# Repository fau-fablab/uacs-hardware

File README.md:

uacs
====

An universal access control system.

Usecase(s)
----------

* machine access control system:
  * monitor access to the machine
  * monitor the machine use time and whether the machine is in use or not
  * add the possibility to reserve machines
  * add a dead man's switch to the machine (force the user to interact with the uacs terminal every x minutes)

Features
--------

* [2.8" Touchscreen](../v2.0/pcb/datasheets/ILI9341.pdf)
* [ISO/IEC 14443A/MIFARE Reader/Writer (supports e.g. MIFARE Classic + DESFire)](../v2.0/pcb/datasheets/PN532-short.pdf)
* [ethernet-access](../v2.0/pcb/datasheets/W5100.pdf)
* powered via 2.1mm DC-Jack (Voltage: 7-50V) or passive POE (power over ethernet)
* micro-sd-card reader to store data (lcd-background images, caching of authorized rfid cards, ..)
* multiple IOs (I²C, UART, SPI, digital/analog pins e.g. to control relais or get sensor values)
* (piezo-)speaker for audio feedback
* real time clock

Remark
------

Development is still in progress, this is not a final version!<br />
If you want to contribute, take a look at the [wiki](https://github.com/fau-fablab/uacs/wiki/Contribution).

PCB
---

The terminal is built from two stacked pcbs in order to save space.<br />
Eagle Layout files and datasheets of used components can be found under [/pcb](../v2.0/pcb).

Firmware
--------

The firmware is written in arduino (c/c++) since the pcb is arduino mega compatible.<br />
The backend is (not yet ;)) written in Python.<br />
All code can be found under [/firmware](../v2.0/firmware).

License
-------

<br />This work is licensed under a <a rel="license" href="http://creativecommons.org/licenses/by-sa/4.0/">Creative Commons Attribution-ShareAlike 4.0 International License</a>.

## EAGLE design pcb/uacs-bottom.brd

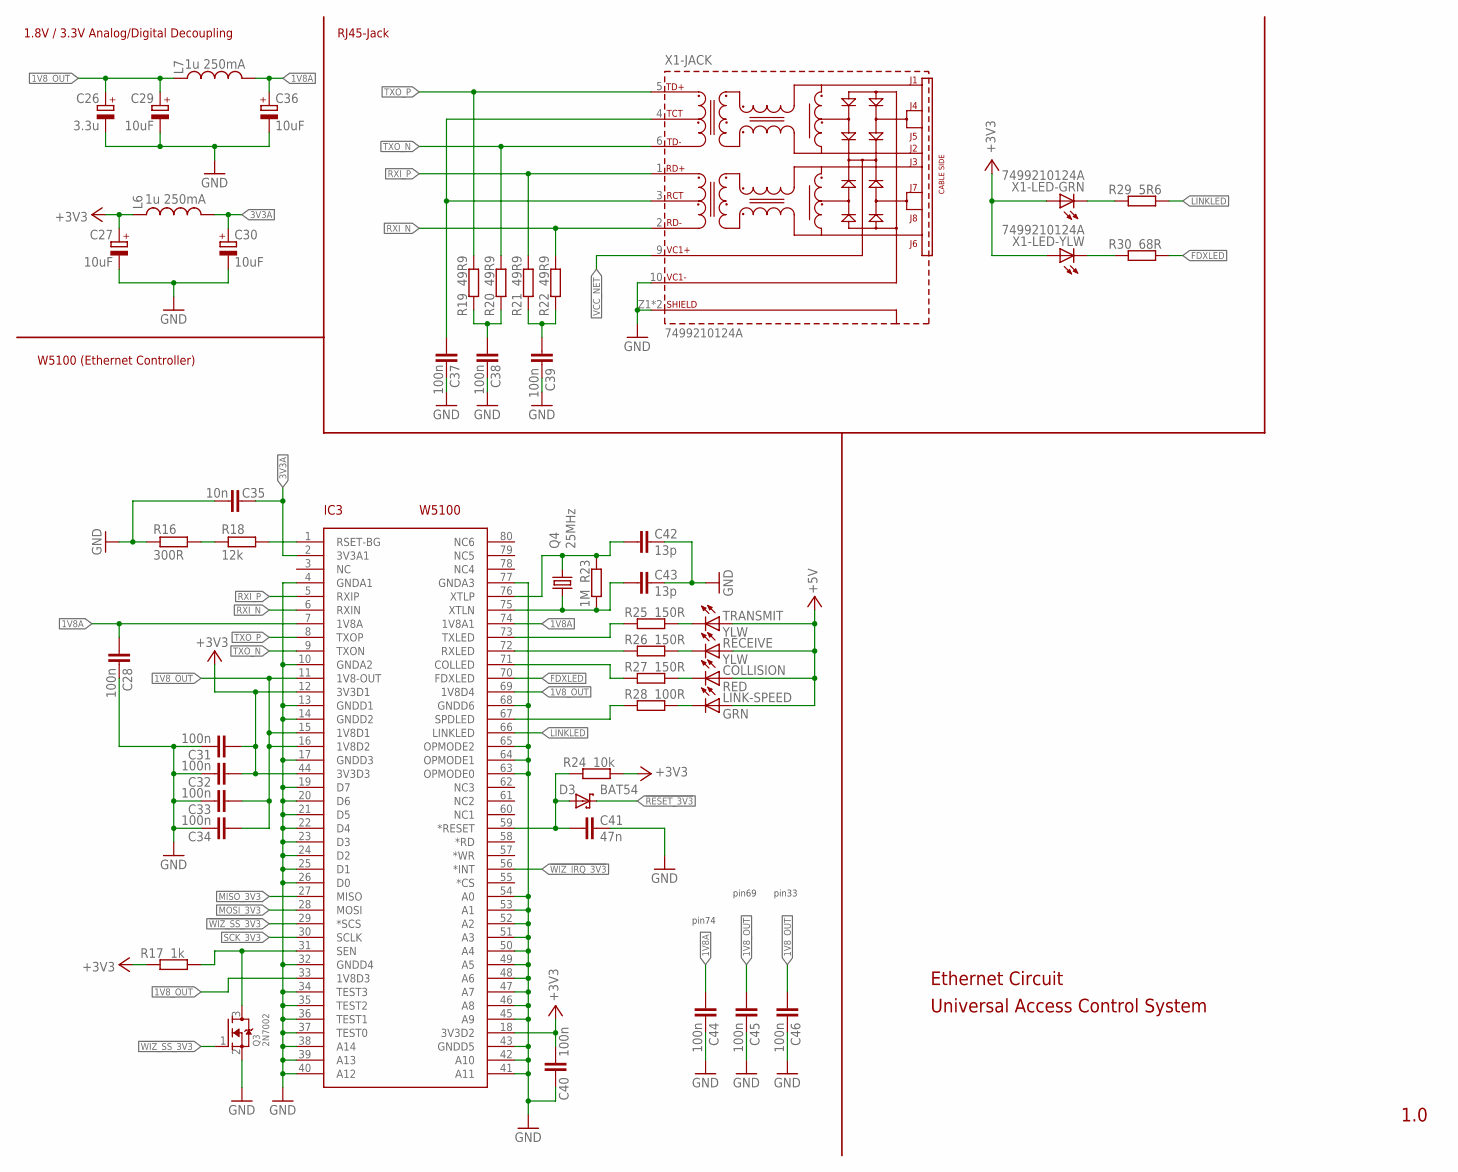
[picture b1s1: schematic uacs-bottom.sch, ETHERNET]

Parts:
C26: 3.3u; B/3528-21R
C27, C29, C30, C36: 10uF; B/3528-21R
C28, C31, C32, C33, C34, C37, C38, C39, C40, C44, C45, C46: 100n; C0603
C35: 10n; C0603
C41: 47n; C0603
C42, C43: 13p; C0603
COLLISION: RED; CHIPLED_0603
D3: BAT54; SOT23
IC3: W5100; SQFP-S-10X10-80
L6, L7: 1u 250mA; 0603
LINK-SPEED: GRN; CHIPLED_0603
Q3: 2N7002; SOT23
Q4: 25MHz; SM49
R16: 300R; R0603
R17: 1k; R0603
R18: 12k; R0603
R19, R20, R21, R22: 49R9; R0603
R23: 1M; R0603
R24: 10k; R0603
R25, R26, R27: 150R; R0603
R28: 100R; R0603
R29: 5R6; R0603
R30: 68R; R0603
RECEIVE: YLW; CHIPLED_0603
TRANSMIT: YLW; CHIPLED_0603
X1: 7499210124A

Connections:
1V8A: C28.1, C36.+, C44.1, IC3.7 (1V8A), IC3.74 (1V8A1), L7.2
1V8_OUT: C26.+, C29.+, C33.1, C34.1, C45.1, C46.1, IC3.11 (1V8-OUT), IC3.15 (1V8D1), IC3.16 (1V8D2), IC3.33 (1V8D3), IC3.69 (1V8D4), L7.1
3V3A: C30.+, C35.1, IC3.2 (3V3A1), L6.2
!RESET_3V3: D3.3 (C)
!WIZ_IRQ_3V3: IC3.56 (*INT)
!WIZ_SS_3V3: IC3.29 (*SCS), Q3.1 (G)
+3V3: C27.+, C31.1, C32.1, C40.1, IC3.12 (3V3D1), IC3.18 (3V3D2), IC3.44 (3V3D3), L6.1, R17.1, R24.2, X1.12 (A), X1.14 (A)
+5V: COLLISION.A, LINK-SPEED.A, RECEIVE.A, TRANSMIT.A
FDXLED: IC3.70 (FDXLED), R30.2
GND: C26.-, C27.-, C28.2, C29.-, C30.-, C31.2, C32.2, C33.2, C34.2, C35.2, C36.-, C37.2, C38.2, C39.2, C40.2, C41.2, C42.2, C43.2, C44.2, C45.2, C46.2, IC3.4 (GNDA1), IC3.10 (GNDA2), IC3.13 (GNDD1), IC3.14 (GNDD2), IC3.17 (GNDD3), IC3.19 (D7), IC3.20 (D6), IC3.21 (D5), IC3.22 (D4), IC3.23 (D3), IC3.24 (D2), IC3.25 (D1), IC3.26 (D0), IC3.32 (GNDD4), IC3.34 (TEST3), IC3.35 (TEST2), IC3.36 (TEST1), IC3.37 (TEST0), IC3.38 (A14), IC3.39 (A13), IC3.40 (A12), IC3.41 (A11), IC3.42 (A10), IC3.43 (GNDD5), IC3.45 (A9), IC3.46 (A8), IC3.47 (A7), IC3.48 (A6), IC3.49 (A5), IC3.50 (A4), IC3.51 (A3), IC3.52 (A2), IC3.53 (A1), IC3.54 (A0), IC3.63 (OPMODE0), IC3.64 (OPMODE1), IC3.65 (OPMODE2), IC3.68 (GNDD6), IC3.77 (GNDA3), Q3.2 (S), R16.1, X1.10 (VC1-), X1.Z1 (SHIELD), X1.Z2 (SHIELD)
LINKLED: IC3.66 (LINKLED), R29.2
MISO_3V3: IC3.27 (MISO)
MOSI_3V3: IC3.28 (MOSI)
unnamed: IC3.1 (RSET-BG), R18.2
unnamed: R30.1, X1.13 (C)
unnamed: R29.1, X1.11 (C)
unnamed: C41.1, D3.1 (A), IC3.59 (*RESET), R24.1
unnamed: C39.1, R21.1, R22.1
unnamed: R25.2, TRANSMIT.C
unnamed: C38.1, R19.1, R20.1
unnamed: IC3.67 (SPDLED), R28.1
unnamed: R26.2, RECEIVE.C
unnamed: IC3.71 (COLLED), R27.1
unnamed: IC3.72 (RXLED), R26.1
unnamed: IC3.73 (TXLED), R25.1
unnamed: COLLISION.C, R27.2
unnamed: LINK-SPEED.C, R28.2
unnamed: C43.1, IC3.75 (XTLN), Q4.1, R23.1
unnamed: C42.1, IC3.76 (XTLP), Q4.2, R23.2
unnamed: R16.2, R18.1
RXI_N: IC3.6 (RXIN), R22.2, X1.2 (RD-)
RXI_P: IC3.5 (RXIP), R21.2, X1.1 (RD+)
SCK_3V3: IC3.30 (SCLK)
SEN: IC3.31 (SEN), Q3.3 (D), R17.2
TXCT: C37.1, X1.3 (RCT), X1.4 (TCT)
TXO_N: IC3.9 (TXON), R20.2, X1.6 (TD-)
TXO_P: IC3.8 (TXOP), R19.2, X1.5 (TD+)
VCC_NET: X1.9 (VC1+)

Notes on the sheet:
1.8V / 3.3V Analog/Digital Decoupling
RJ45-Jack
W5100 (Ethernet Controller)
Ethernet Circuit
1.0
pin74
pin69
pin33
Universal Access Control System

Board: 2 copper layers, 47 parts (0 on the bottom side), 32 nets, no tracks yet.

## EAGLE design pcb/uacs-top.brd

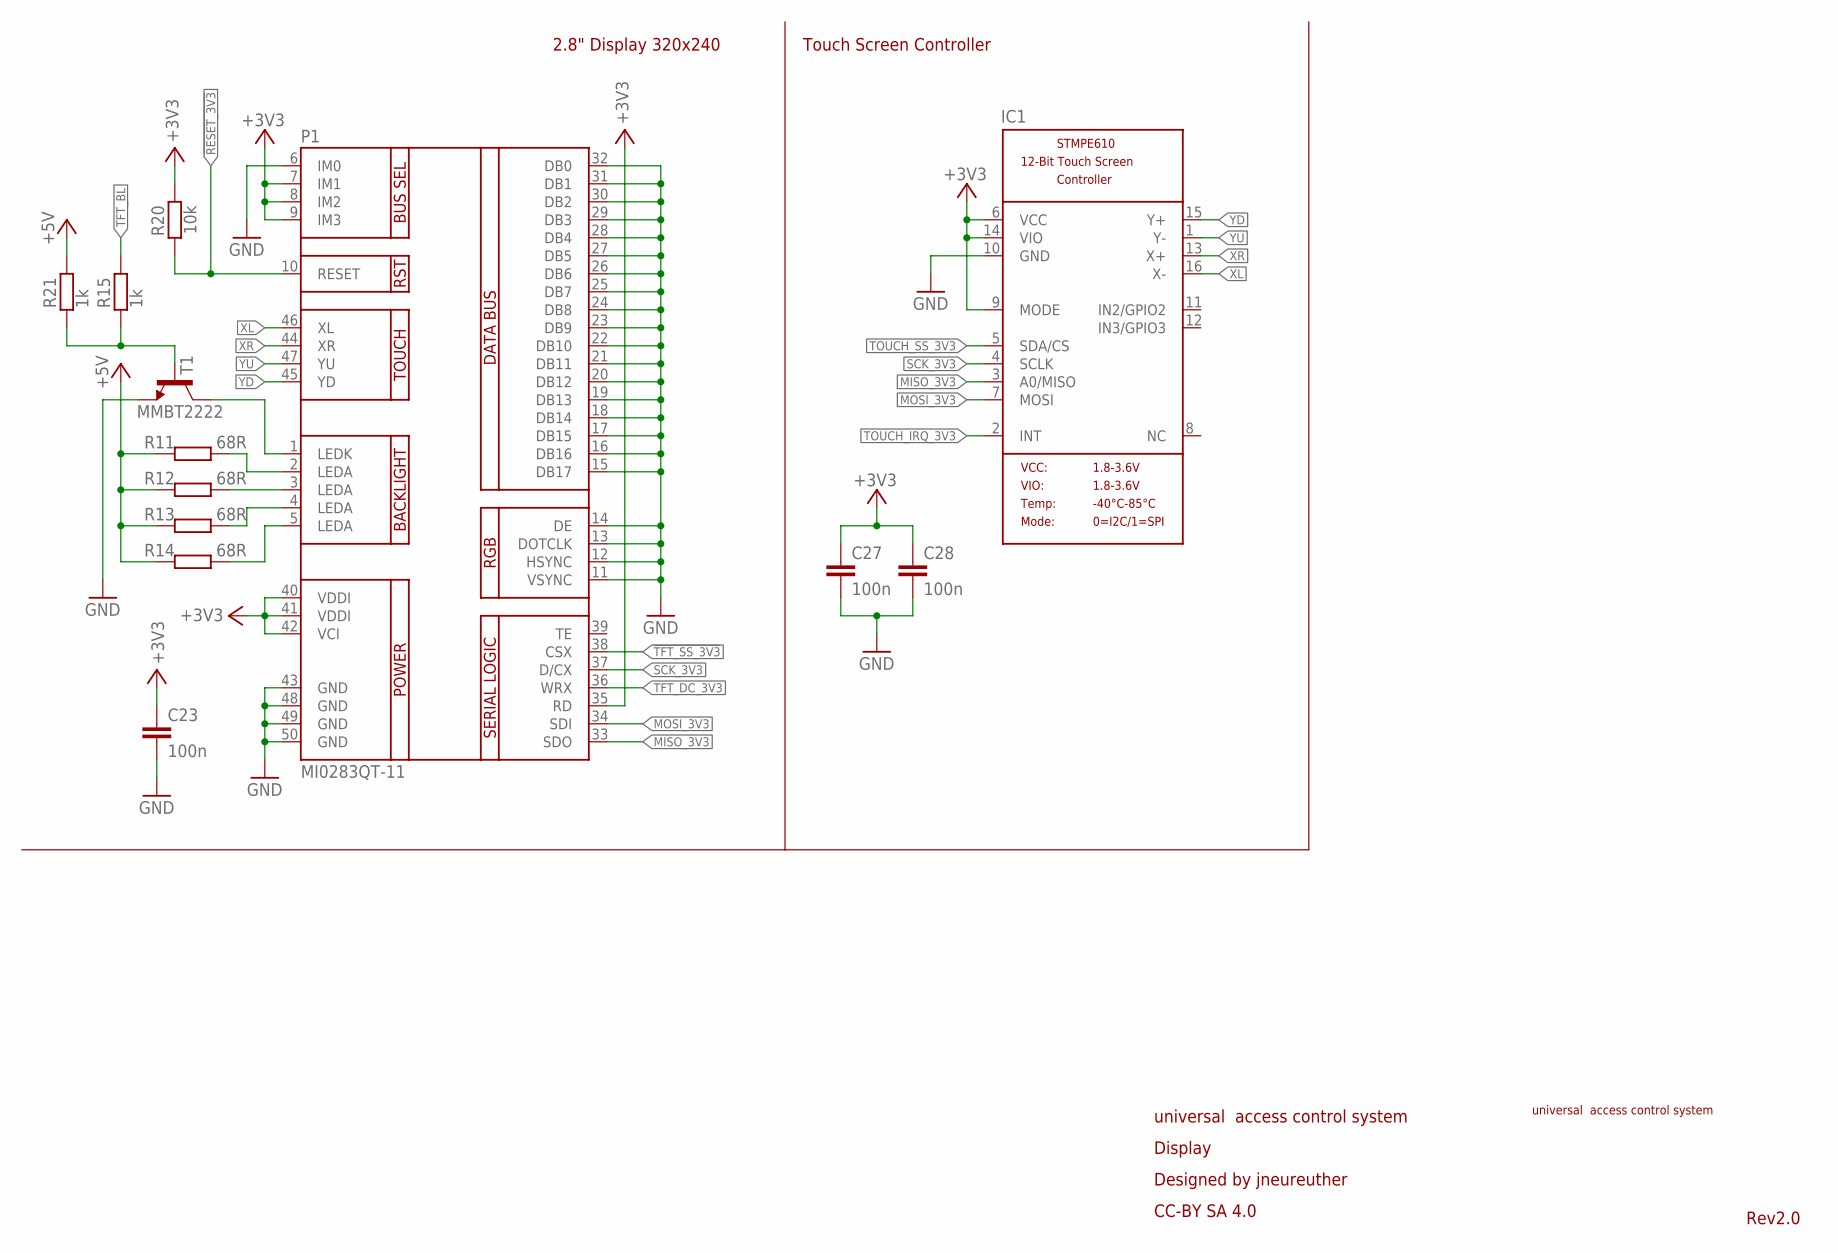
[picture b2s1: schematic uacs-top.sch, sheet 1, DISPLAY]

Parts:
C23, C27, C28: 100n; C0603
IC1: STMPE610; QFN16_3MM
P1: MI0283QT-11
R11, R12, R13, R14: 68R; R0603
R15, R21: 1k; R0603
R20: 10k; R0603
T1: MMBT2222; SOT23-BEC

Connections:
!RESET_3V3: P1.10 (RESET), R20.1; also elsewhere on the board
!TFT_SS_3V3: P1.38 (CSX)
+3V3: C23.1, C27.1, C28.1, IC1.6 (VCC), IC1.9 (MODE), IC1.14 (VIO), P1.7 (IM1), P1.8 (IM2), P1.9 (IM3), P1.35 (RD), P1.40 (VDDI), P1.41 (VDDI), P1.42 (VCI), R20.2; also elsewhere on the board
+5V: R11.1, R12.1, R13.1, R14.1, R21.1; also elsewhere on the board
GND: C23.2, C27.2, C28.2, IC1.10 (GND), P1.6 (IM0), P1.11 (VSYNC), P1.12 (HSYNC), P1.13 (DOTCLK), P1.14 (DE), P1.15 (DB17), P1.16 (DB16), P1.17 (DB15), P1.18 (DB14), P1.19 (DB13), P1.20 (DB12), P1.21 (DB11), P1.22 (DB10), P1.23 (DB9), P1.24 (DB8), P1.25 (DB7), P1.26 (DB6), P1.27 (DB5), P1.28 (DB4), P1.29 (DB3), P1.30 (DB2), P1.31 (DB1), P1.32 (DB0), P1.43 (GND), P1.48 (GND), P1.49 (GND), P1.50 (GND), T1.E; also elsewhere on the board
MISO_3V3: IC1.3 (A0/MISO), P1.33 (SDO); also elsewhere on the board
MOSI_3V3: IC1.7 (MOSI), P1.34 (SDI); also elsewhere on the board
unnamed: P1.5 (LEDA), R14.2
unnamed: P1.4 (LEDA), R13.2
unnamed: P1.3 (LEDA), R12.2
unnamed: P1.2 (LEDA), R11.2
unnamed: P1.1 (LEDK), T1.C
unnamed: R15.2, R21.2, T1.B
SCK_3V3: IC1.4 (SCLK), P1.37 (D/CX); also elsewhere on the board
TFT_BL: R15.1; also elsewhere on the board
TFT_DC_3V3: P1.36 (WRX); also elsewhere on the board
TOUCH_IRQ_3V3: IC1.2 (INT); also elsewhere on the board
TOUCH_SS_3V3: IC1.5 (SDA/CS); also elsewhere on the board
XL: IC1.16 (X-), P1.46 (XL)
XR: IC1.13 (X+), P1.44 (XR)
YD: IC1.15 (Y+), P1.45 (YD)
YU: IC1.1 (Y-), P1.47 (YU)

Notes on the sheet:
universal access control system
Rev2.0
universal access control system Display Designed by jneureuther CC-BY SA 4.0
2.8" Display 320x240
Touch Screen Controller

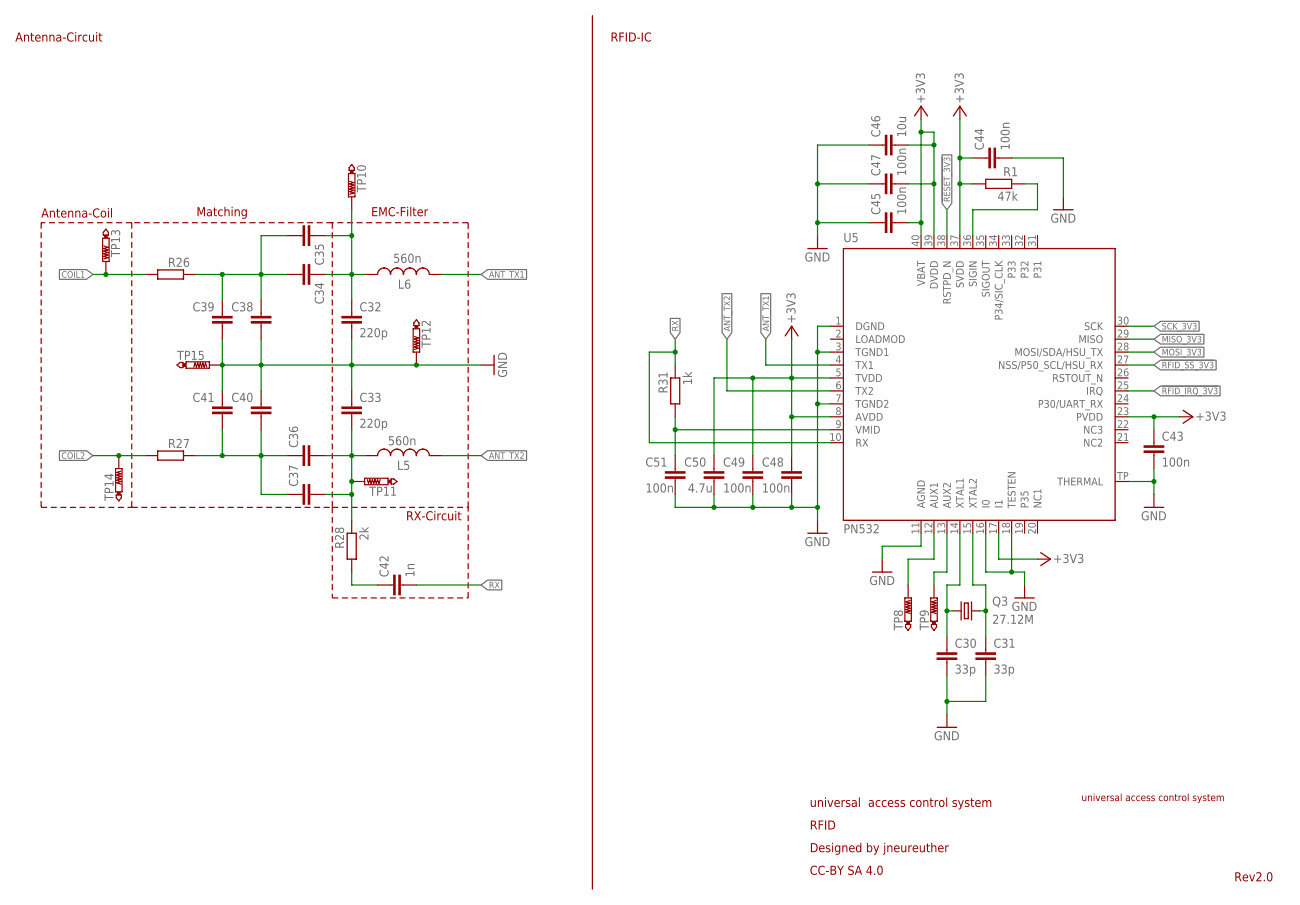
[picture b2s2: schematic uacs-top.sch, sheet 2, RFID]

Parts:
C30, C31: 33p; C0603
C32, C33: 220p; C0603
C34, C35, C36, C37, C38, C39, C40, C41: C-EUC0603; C0603
C42: 1n; C0603
C43, C44, C45, C47, C48, C49, C51: 100n; C0603
C46: 10u; C0603
C50: 4.7u; C0603
L5, L6: 560n; 0805
Q3: 27.12M; CTS406
R1: 47k; R0603
R26, R27: R-EU_R0603; R0603
R28: 2k; R0603
R31: 1k; R0603
TP8, TP9, TP10, TP11, TP12, TP13, TP14, TP15: PTR1TP20R; TP20R
U5: PN532; HVQFN40-6X6

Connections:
!RESET_3V3: U5.38 (RSTPD_N); also elsewhere on the board
!RFID_IRQ_3V3: U5.25 (IRQ); also elsewhere on the board
!RFID_SS_3V3: U5.27 (NSS/P50_SCL/HSU_RX); also elsewhere on the board
+3V3: C43.1, C44.1, C45.2, C46.2, C47.2, C48.1, C49.1, C50.1, R1.2, U5.5 (TVDD), U5.8 (AVDD), U5.17 (I1), U5.23 (PVDD), U5.37 (SVDD), U5.39 (DVDD), U5.40 (VBAT); also elsewhere on the board
ANT_TX1: L6.1, U5.4 (TX1)
ANT_TX2: L5.1, U5.6 (TX2)
COIL1: R26.2, TP13.TP
COIL2: R27.2, TP14.TP
GND: C30.2, C31.2, C32.2, C33.1, C38.2, C39.2, C40.1, C41.1, C43.2, C44.2, C45.1, C46.1, C47.1, C48.2, C49.2, C50.2, C51.2, TP12.TP, TP15.TP, U5.1 (DGND), U5.3 (TGND1), U5.7 (TGND2), U5.11 (AGND), U5.16 (I0), U5.18 (TESTEN), U5.TP (THERMAL); also elsewhere on the board
MISO_3V3: U5.29 (MISO); also elsewhere on the board
MOSI_3V3: U5.28 (MOSI/SDA/HSU_TX); also elsewhere on the board
unnamed: R1.1, U5.36 (SIGIN)
unnamed: C42.1, R28.2
unnamed: TP8.TP, U5.12 (AUX1)
unnamed: TP9.TP, U5.13 (AUX2)
unnamed: C33.2, C36.2, C37.2, L5.2, R28.1, TP11.TP
unnamed: C32.1, C34.1, C35.1, L6.2, TP10.TP
unnamed: C51.1, R31.2, U5.9 (VMID)
unnamed: C34.2, C35.2, C38.1, C39.1, R26.1
unnamed: C30.1, Q3.1, U5.14 (XTAL1)
unnamed: C31.1, Q3.3 (2), U5.15 (XTAL2)
unnamed: C36.1, C37.1, C40.2, C41.2, R27.1
RX: C42.2, R31.1, U5.10 (RX)
SCK_3V3: U5.30 (SCK); also elsewhere on the board

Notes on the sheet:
EMC-Filter
Matching
RX-Circuit
Antenna-Coil
universal access control system RFID Designed by jneureuther CC-BY SA 4.0
Rev2.0
universal access control system
RFID-IC
Antenna-Circuit

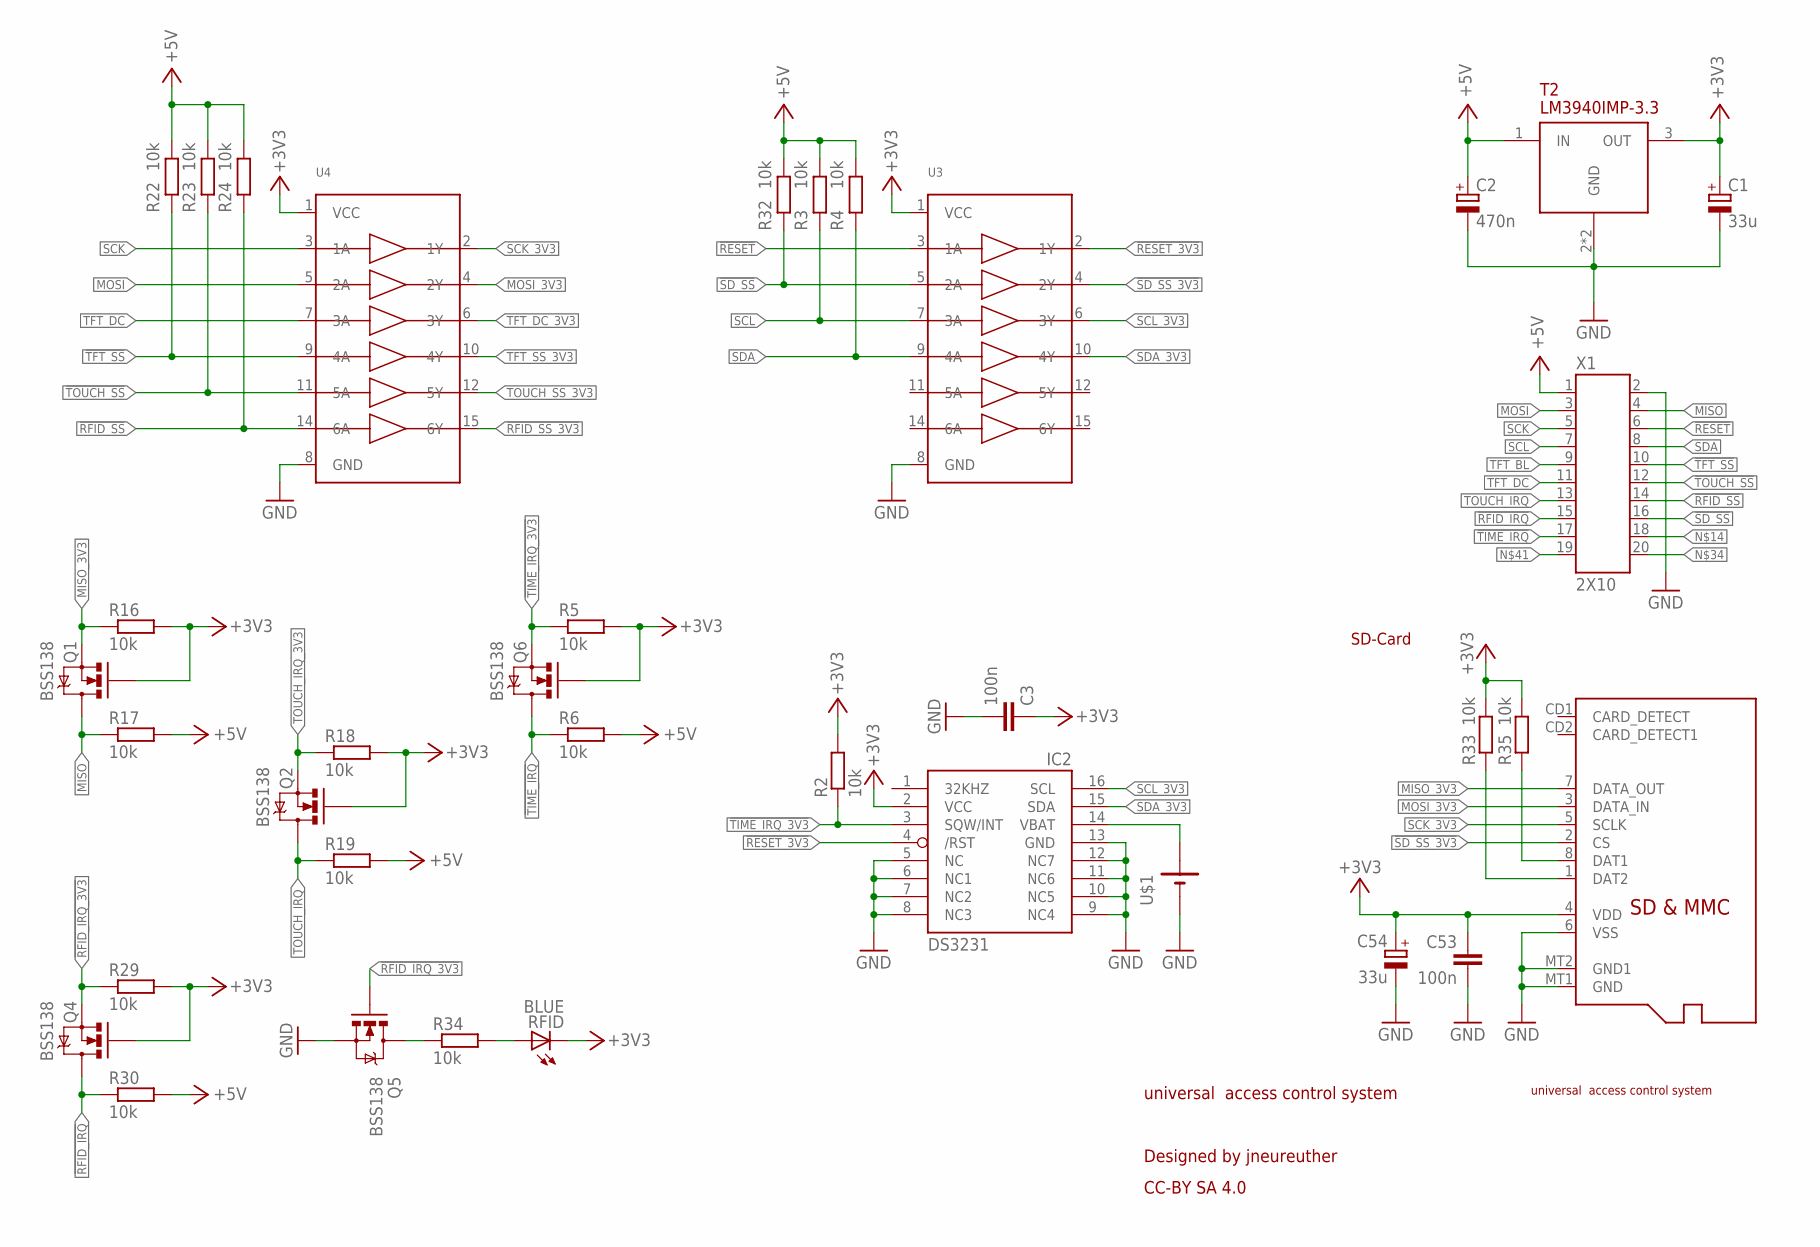
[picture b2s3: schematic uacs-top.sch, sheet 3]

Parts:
C1: 33u; PANASONIC_D
C2: 470n; PANASONIC_B
C3, C53: 100n; C0603
C54: 33u; C/6032-28R
IC2: DS3231/SO; SO16W
Q1, Q2, Q4, Q5, Q6: BSS138; SOT23
R2, R3, R4, R5, R6, R16, R17, R18, R19, R22, R23, R24, R29, R30, R32, R33, R34, R35: 10k; R0603
RFID: BLUE; CHIP-LED0603
T2: LM3940IMP-3.3; SOT223
U3, U4: 74HC4050D; SOIC16
U$1: CR1220SMT; CR1220-SMD
X1: 2X10
X3: MICROSD

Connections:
!RESET: U3.3 (1A), X1.6
!RESET_3V3: IC2.4 (/RST), U3.2 (1Y); also elsewhere on the board
!RFID_IRQ: Q4.3 (D), R30.1, X1.15
!RFID_IRQ_3V3: Q4.2 (S), Q5.1 (G), R29.1; also elsewhere on the board
!RFID_SS: R24.1, U4.14 (6A), X1.14
!RFID_SS_3V3: U4.15 (6Y); also elsewhere on the board
!SD_SS: R32.1, U3.5 (2A), X1.16
!SD_SS_3V3: U3.4 (2Y), X3.2 (CS)
!TFT_SS: R22.1, U4.9 (4A), X1.10
!TIME_IRQ: Q6.3 (D), R6.1, X1.17
!TIME_IRQ_3V3: IC2.3 (SQW/INT), Q6.2 (S), R2.1, R5.1
!TOUCH_SS: R23.1, U4.11 (5A), X1.12
+3V3: C1.+, C3.1, C53.1, C54.+, IC2.2 (VCC), Q1.1 (G), Q2.1 (G), Q4.1 (G), Q6.1 (G), R2.2, R5.2, R16.2, R18.2, R29.2, R33.2, R35.2, RFID.C, T2.3 (OUT), U3.1 (VCC), U4.1 (VCC), X3.4 (VDD); also elsewhere on the board
+5V: C2.+, R3.2, R4.2, R6.2, R17.2, R19.2, R22.2, R23.2, R24.2, R30.2, R32.2, T2.1 (IN), X1.1; also elsewhere on the board
GND: C1.-, C2.-, C3.2, C53.2, C54.-, IC2.5 (NC), IC2.6 (NC1), IC2.7 (NC2), IC2.8 (NC3), IC2.9 (NC4), IC2.10 (NC5), IC2.11 (NC6), IC2.12 (NC7), IC2.13 (GND), Q5.2 (S), T2.2 (GND), T2.4 (GND), U3.8 (GND), U4.8 (GND), U$1.- (VSS), X1.2, X3.6 (VSS), X3.MT1 (GND), X3.MT2 (GND1); also elsewhere on the board
MISO: Q1.3 (D), R17.1, X1.4
MISO_3V3: Q1.2 (S), R16.1, X3.7 (DATA_OUT); also elsewhere on the board
MOSI: U4.5 (2A), X1.3
MOSI_3V3: U4.4 (2Y), X3.3 (DATA_IN); also elsewhere on the board
unnamed: IC2.14 (VBAT), U$1.+$1 (VCC), U$1.+$2 (VCC)
unnamed: R35.1, X3.8 (DAT1)
unnamed: R34.2, RFID.A
unnamed: R33.1, X3.1 (DAT2)
unnamed: Q5.3 (D), R34.1
SCK: U4.3 (1A), X1.5
SCK_3V3: U4.2 (1Y), X3.5 (SCLK); also elsewhere on the board
SCL: R3.1, U3.7 (3A), X1.7
SCL_3V3: IC2.16 (SCL), U3.6 (3Y)
SDA: R4.1, U3.9 (4A), X1.8
SDA_3V3: IC2.15 (SDA), U3.10 (4Y)
TFT_BL: X1.9; also elsewhere on the board
TFT_DC: U4.7 (3A), X1.11
TFT_DC_3V3: U4.6 (3Y); also elsewhere on the board
TFT_SS_3V3: U4.10 (4Y)
TOUCH_IRQ: Q2.3 (D), R19.1, X1.13
TOUCH_IRQ_3V3: Q2.2 (S), R18.1; also elsewhere on the board
TOUCH_SS_3V3: U4.12 (5Y); also elsewhere on the board

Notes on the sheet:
SD-Card
universal access control system Designed by jneureuther CC-BY SA 4.0
universal access control system

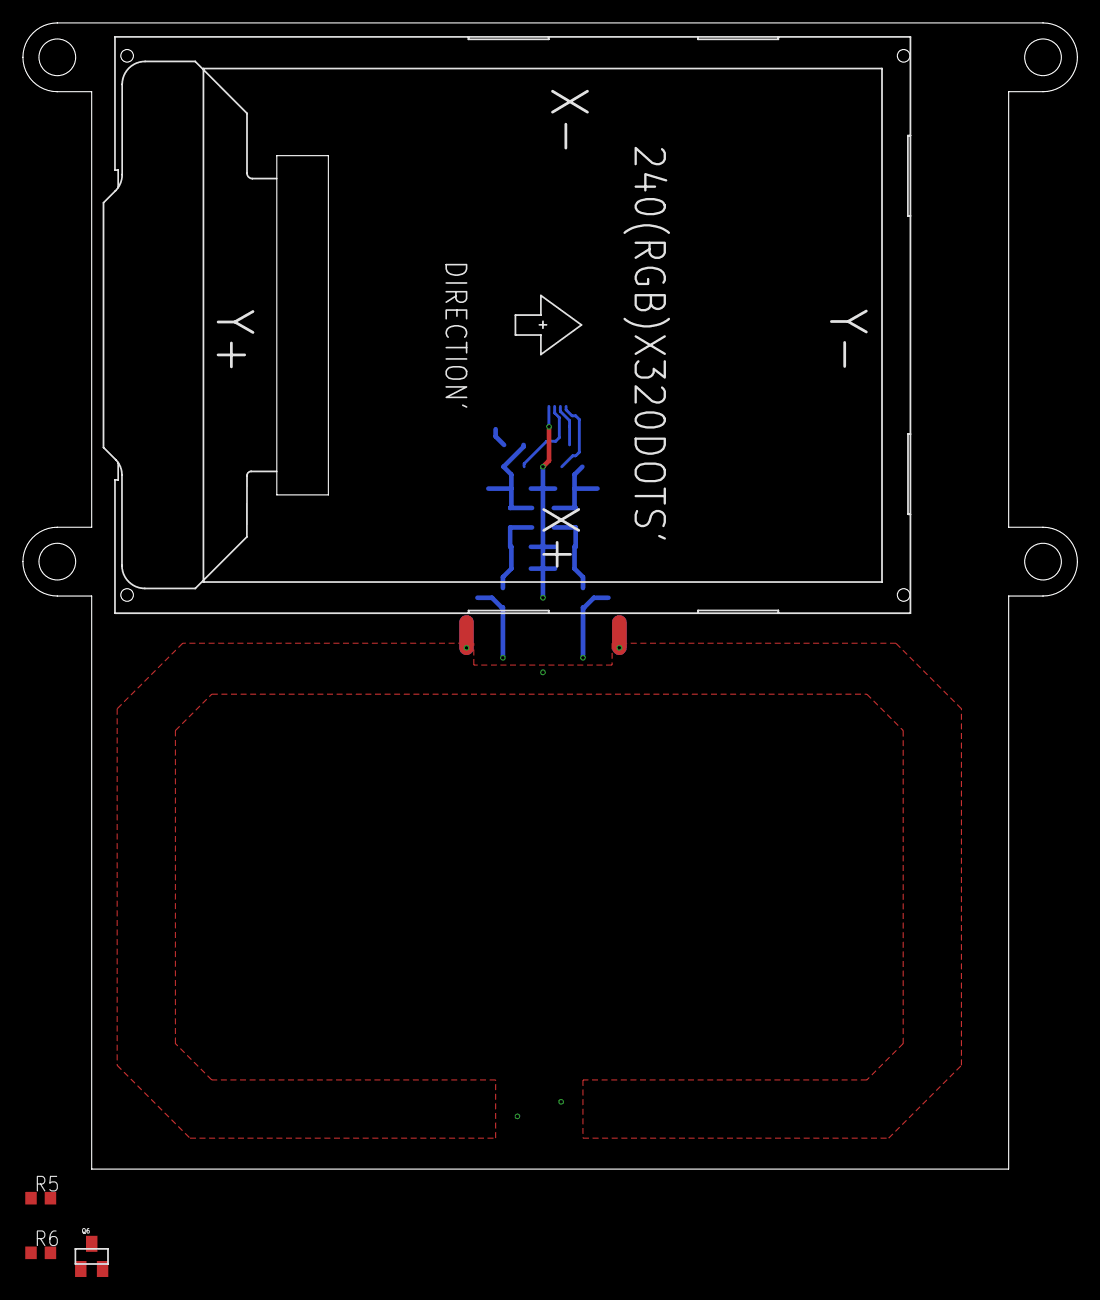
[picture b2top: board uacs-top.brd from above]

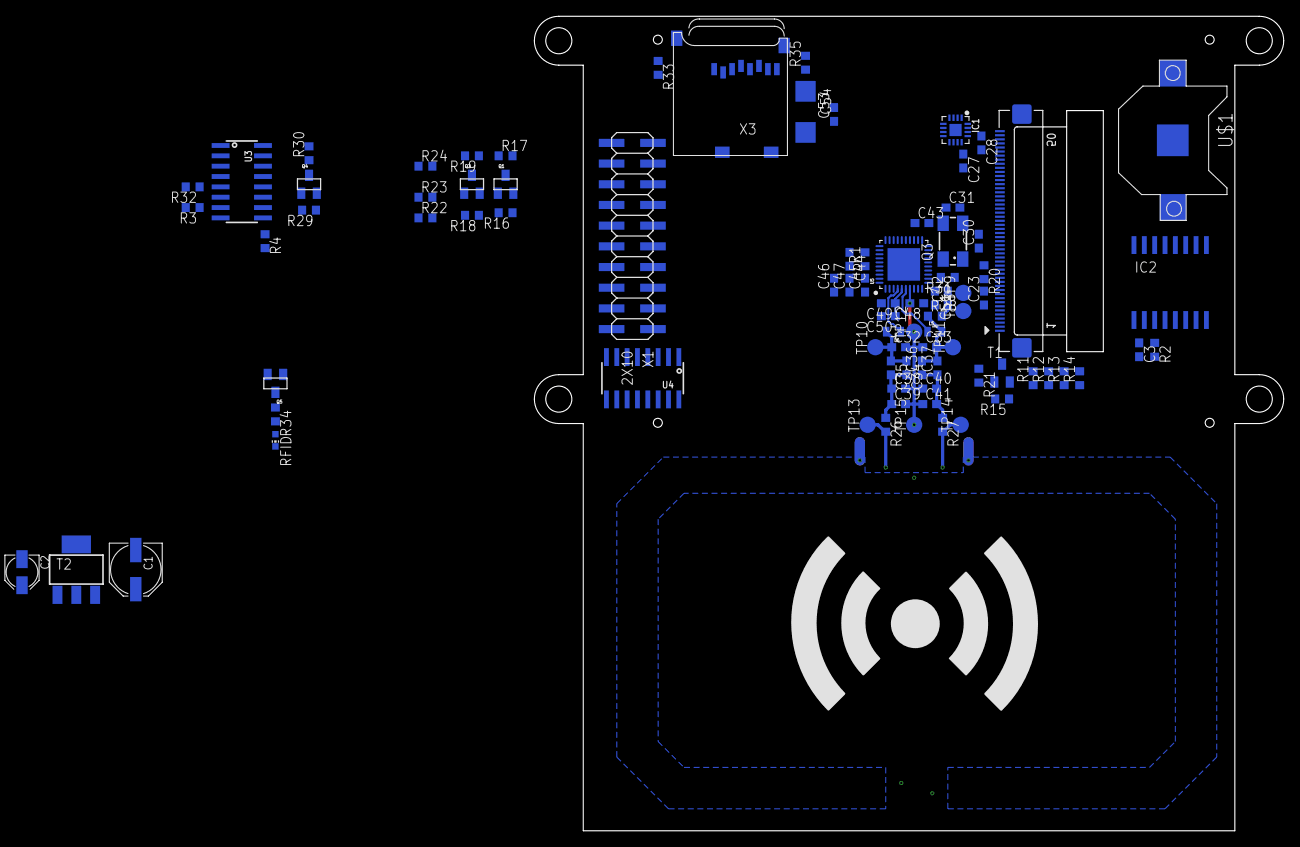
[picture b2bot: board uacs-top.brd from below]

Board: 4 copper layers, 92.0 x 100.0 mm, 88 parts (84 on the bottom side), 62 nets.

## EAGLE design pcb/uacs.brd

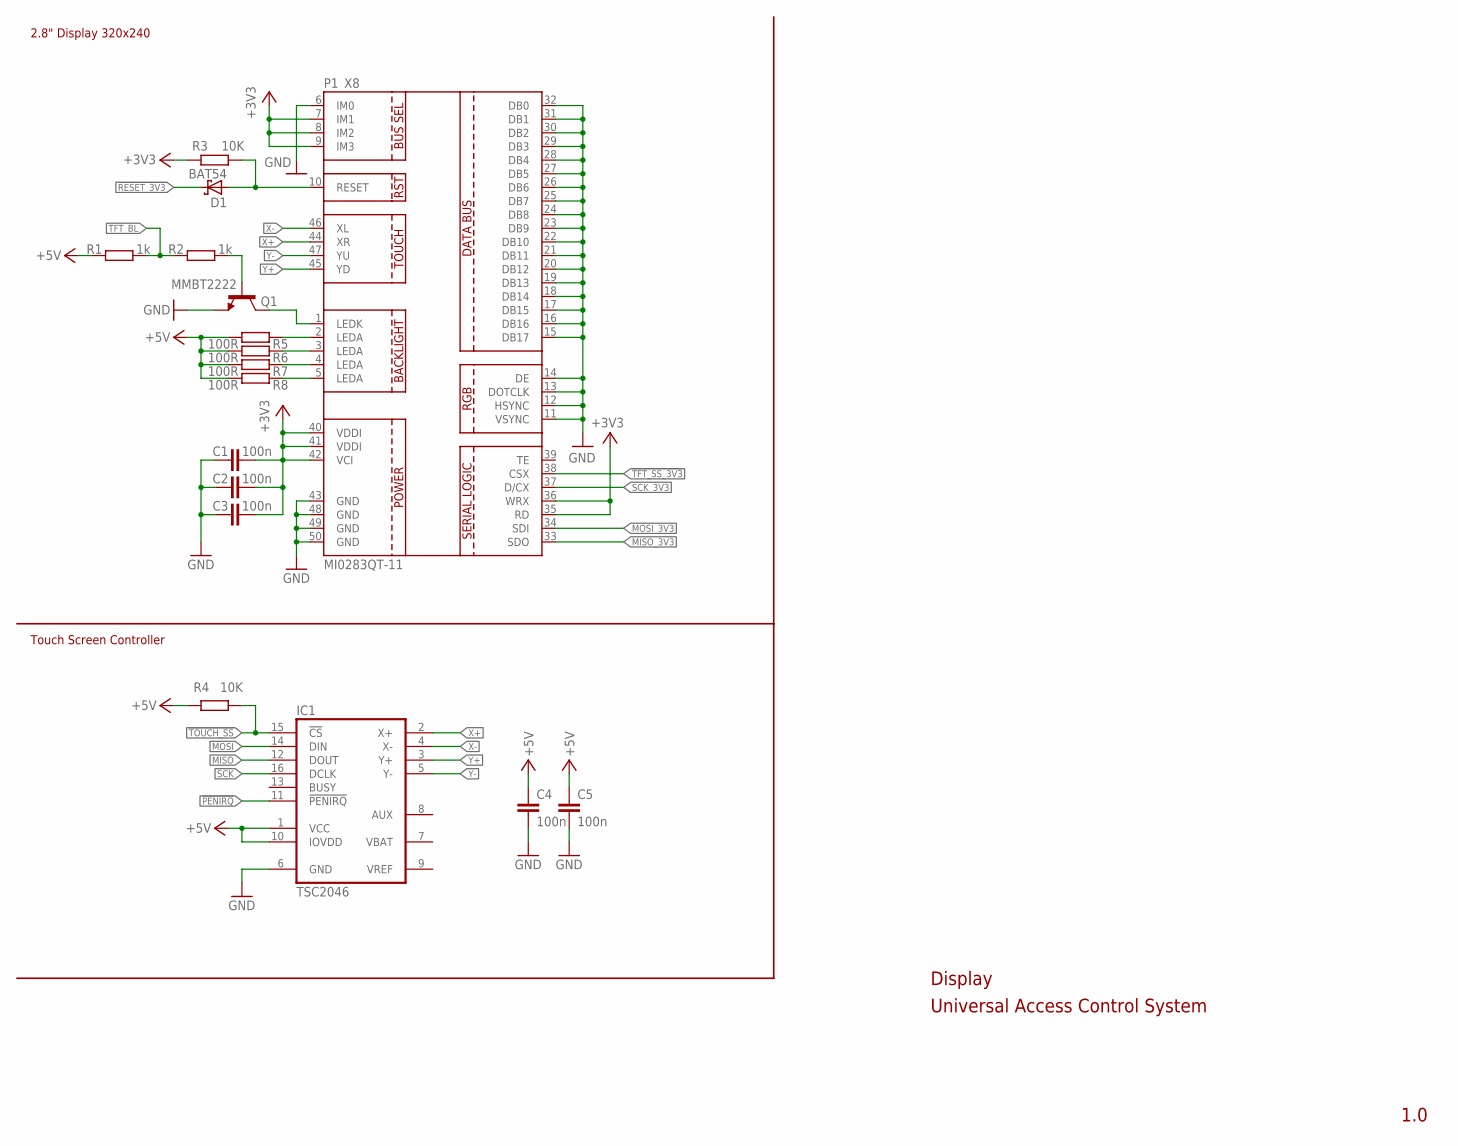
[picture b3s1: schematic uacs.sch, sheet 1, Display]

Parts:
C1, C2, C3, C4, C5: 100n; C0603
D1: BAT54; SOT23
IC1: TSC2046; TSSOP16
P1: MI0283QT-11
Q1: MMBT2222; SOT23-3
R1, R2: 1k; R0603
R3, R4: 10K; R0603
R5, R6, R7, R8: 100R; R0603

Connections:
!PENIRQ: IC1.11 (!PENIRQ); also elsewhere on the board
!RESET_3V3: D1.3 (C); also elsewhere on the board
!TFT_SS_3V3: P1.38 (CSX); also elsewhere on the board
!TOUCH_SS: IC1.15 (!CS), R4.1; also elsewhere on the board
+3V3: C1.2, C2.2, C3.2, P1.7 (IM1), P1.8 (IM2), P1.9 (IM3), P1.35 (RD), P1.36 (WRX), P1.40 (VDDI), P1.41 (VDDI), P1.42 (VCI), R3.2; also elsewhere on the board
+5V: C4.1, C5.1, IC1.1 (VCC), IC1.10 (IOVDD), R1.1, R4.2, R5.2, R6.2, R7.2, R8.2; also elsewhere on the board
GND: C1.1, C2.1, C3.1, C4.2, C5.2, IC1.6 (GND), P1.6 (IM0), P1.11 (VSYNC), P1.12 (HSYNC), P1.13 (DOTCLK), P1.14 (DE), P1.15 (DB17), P1.16 (DB16), P1.17 (DB15), P1.18 (DB14), P1.19 (DB13), P1.20 (DB12), P1.21 (DB11), P1.22 (DB10), P1.23 (DB9), P1.24 (DB8), P1.25 (DB7), P1.26 (DB6), P1.27 (DB5), P1.28 (DB4), P1.29 (DB3), P1.30 (DB2), P1.31 (DB1), P1.32 (DB0), P1.43 (GND), P1.48 (GND), P1.49 (GND), P1.50 (GND), Q1.2 (E); also elsewhere on the board
MISO: IC1.12 (DOUT); also elsewhere on the board
MISO_3V3: P1.33 (SDO); also elsewhere on the board
MOSI: IC1.14 (DIN); also elsewhere on the board
MOSI_3V3: P1.34 (SDI); also elsewhere on the board
unnamed: P1.1 (LEDK), Q1.3 (C)
unnamed: P1.5 (LEDA), R8.1
unnamed: Q1.1 (B), R2.2
unnamed: P1.4 (LEDA), R7.1
unnamed: P1.3 (LEDA), R6.1
unnamed: P1.2 (LEDA), R5.1
unnamed: D1.1 (A), P1.10 (RESET), R3.1
SCK: IC1.16 (DCLK); also elsewhere on the board
SCK_3V3: P1.37 (D/CX); also elsewhere on the board
TFT_BL: R1.2, R2.1; also elsewhere on the board
X+: IC1.2 (X+), P1.44 (XR)
X-: IC1.4 (X-), P1.46 (XL)
Y+: IC1.3 (Y+), P1.45 (YD)
Y-: IC1.5 (Y-), P1.47 (YU)

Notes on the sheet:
2.8" Display 320x240
Touch Screen Controller
Display
1.0
Universal Access Control System

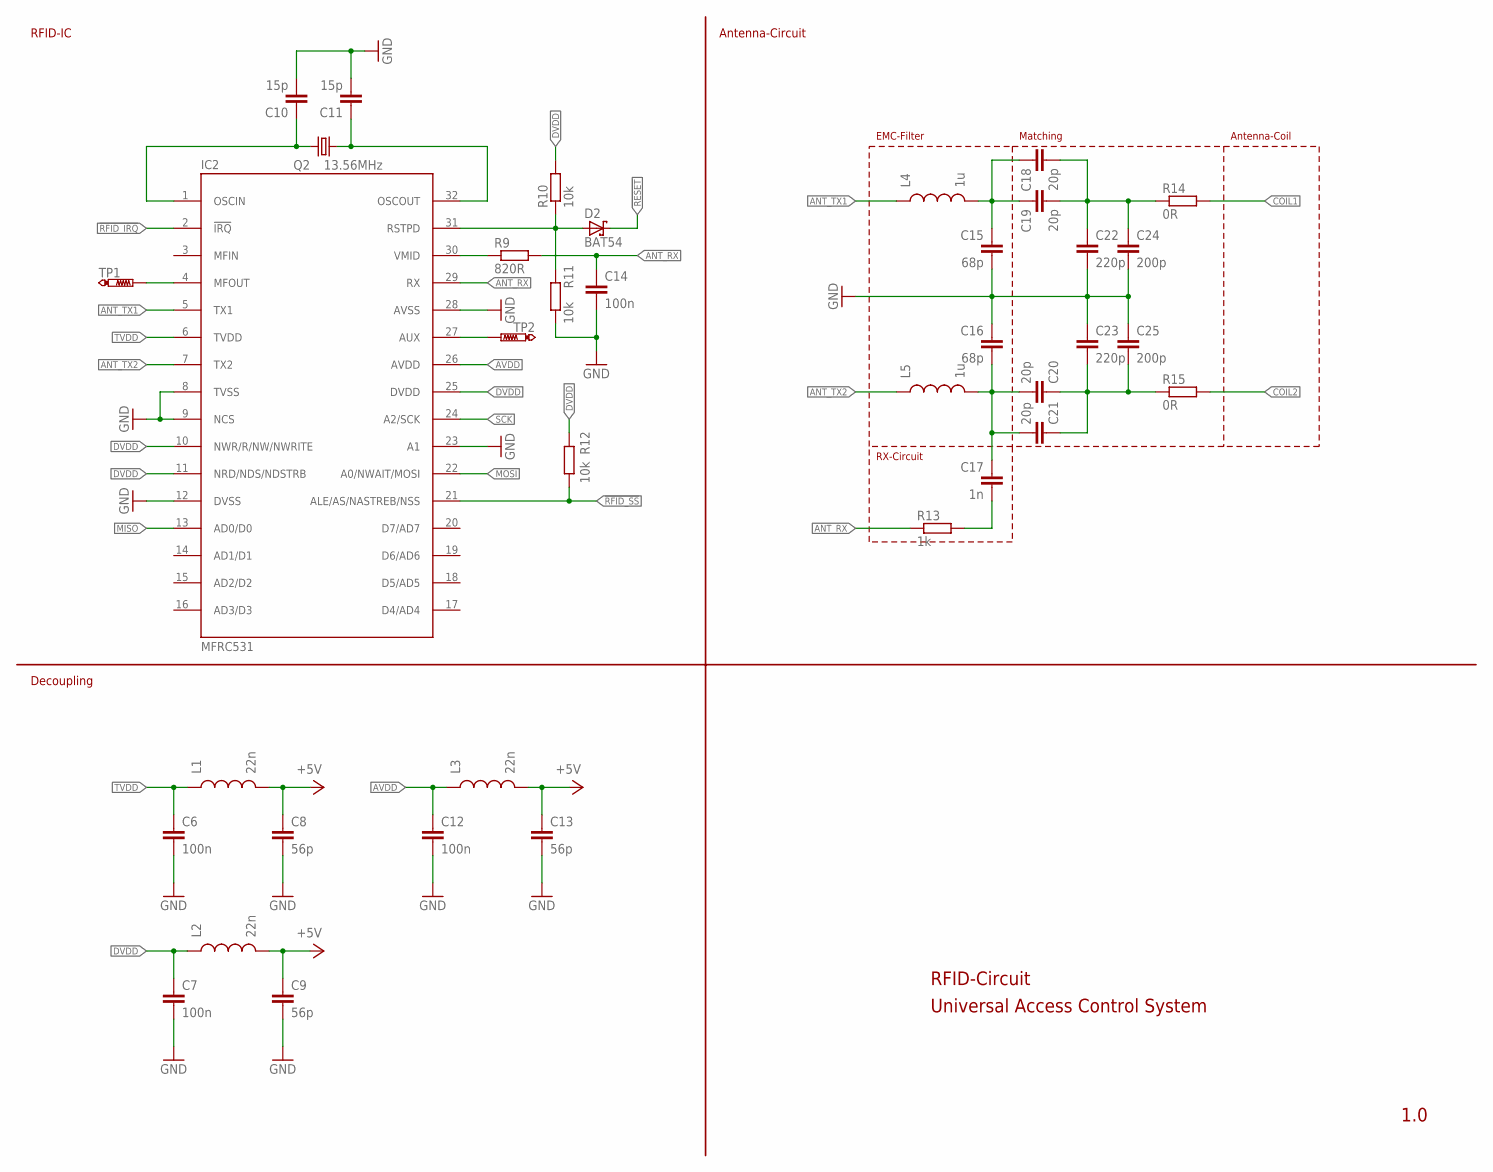
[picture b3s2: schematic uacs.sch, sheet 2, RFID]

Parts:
C6, C7, C12, C14: 100n; C0603
C8, C9, C13: 56p; C0603
C10, C11: 15p; C0603
C15, C16: 68p; C0603
C17: 1n; C0603
C18, C19, C20, C21: 20p; C0603
C22, C23: 220p; C0603
C24, C25: 200p; C0603
D2: BAT54; SOT23
IC2: MFRC531; SO32
L1, L2, L3: 22n; 0603
L4, L5: 1u; 0603
Q2: 13.56MHz; SM49
R9: 820R; R0603
R10, R11, R12: 10k; R0603
R13: 1k; R0603
R14, R15: 0R; R0603
TP1, TP2: PTR1B1,27; B1,27

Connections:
!RESET: D2.3 (C); also elsewhere on the board
!RFID_IRQ: IC2.2 (!IRQ); also elsewhere on the board
!RFID_SS: IC2.21 (ALE/AS/NASTREB/NSS), R12.1; also elsewhere on the board
+5V: C8.1, C9.1, C13.1, L1.2, L2.2, L3.2; also elsewhere on the board
ANT_RX: C14.1, IC2.29 (RX), R9.2, R13.1
ANT_TX1: IC2.5 (TX1), L4.1
ANT_TX2: IC2.7 (TX2), L5.1
AVDD: C12.1, IC2.26 (AVDD), L3.1
COIL1: R14.2
COIL2: R15.2
DVDD: C7.1, IC2.10 (NWR/R/NW/NWRITE), IC2.11 (NRD/NDS/NDSTRB), IC2.25 (DVDD), L2.1, R10.2, R12.2
GND: C6.2, C7.2, C8.2, C9.2, C10.2, C11.2, C12.2, C13.2, C14.2, C15.2, C16.1, C22.2, C23.1, C24.2, C25.1, IC2.8 (TVSS), IC2.9 (NCS), IC2.12 (DVSS), IC2.23 (A1), IC2.28 (AVSS), R11.1; also elsewhere on the board
MISO: IC2.13 (AD0/D0); also elsewhere on the board
MOSI: IC2.22 (A0/NWAIT/MOSI); also elsewhere on the board
unnamed: D2.1 (A), IC2.31 (RSTPD), R10.1, R11.2
unnamed: C11.1, IC2.32 (OSCOUT), Q2.1
unnamed: IC2.4 (MFOUT), TP1.TP
unnamed: IC2.30 (VMID), R9.1
unnamed: IC2.27 (AUX), TP2.TP
unnamed: C16.2, C17.1, C20.2, C21.2, L5.2
unnamed: C17.2, R13.2
unnamed: C15.1, C18.1, C19.1, L4.2
unnamed: C18.2, C19.2, C22.1, C24.1, R14.1
unnamed: C20.1, C21.1, C23.2, C25.2, R15.1
unnamed: C10.1, IC2.1 (OSCIN), Q2.2
SCK: IC2.24 (A2/SCK); also elsewhere on the board
TVDD: C6.1, IC2.6 (TVDD), L1.1

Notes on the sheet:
EMC-Filter
Matching
RX-Circuit
Antenna-Coil
RFID-IC
Antenna-Circuit
Decoupling
RFID-Circuit
1.0
Universal Access Control System

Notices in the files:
parts and their libraries:
SparkFun-Passives: Licensing: Creative Commons ShareAlike 4.0 International - https://creativecommons.org/licenses/by-sa/4.0
EagleLibrary_Wuerth_Elektronik_eiSos_V6_: Copyright: Würth Elektronik
